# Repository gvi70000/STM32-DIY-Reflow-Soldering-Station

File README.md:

# STM32-DIY-Reflow-Soldering-Station

Warning: Electrical Safety Notice

Before attempting to build or operate the DIY reflow soldering station described in this article, it is imperative to be aware that the hardware operates at 220V AC. Working with high-voltage systems poses inherent risks and demands a thorough understanding of electrical safety precautions.

Introduction:

For electronics enthusiasts seeking a precise and customizable reflow soldering experience, constructing a DIY reflow soldering station is an exciting project. This article provides a detailed overview of the key components and their functionalities, offering a comprehensive guide for building your own soldering station.

Power Supply:

The 220V AC is supplied through the AC Power Entry Module IEC-320 C-14 BVA01/Z0000/02. A Transformer Myrra 47152 steps down the voltage to a crucial 5V, supplying power to essential components such as the BluePill with STM32F302 microcontroller board, fan, and the G3MB-202P 5V DC 1 Channel Solid-State Relay.

User Interface:

The station features a user-friendly interface displayed on a 1.8" ST7735 LCD. User inputs are facilitated through an encoder PEC11R-4220F-S0024 and an RS PRO 17mm Black Potentiometer Knob for 6mm Shaft with a D-shaped grip, ensuring precise control over the soldering process.
Temperature Control and Cooling:

Maintaining optimal temperature is achieved through two strategically positioned 100K ohm 3950 NTC's, calibrated with meticulous accuracy using an FLUKE 51 II Thermometer as a reference. The reflow soldering station incorporates a CFM-6020S-040-320 fan, intelligently activated to cool down the hot plate when needed, ensuring temperature stability.

Operational Modes:

The DIY reflow soldering station offers two distinct modes: rework and reflow. In rework mode, the temperature is kept at a preset value, allowing for precise touch-up soldering. In reflow mode, the temperature follows a preset profile, ideal for soldering components with specific temperature requirements. Both modes utilize a PID controller, ensuring consistent and accurate temperature control throughout the soldering process.

Connections:

The intricate network of connections ensures seamless communication and control within the system. Notable connections include those for SD Card, Encoder, ADC for NTCs, Fan control, Hot plate power control, Buzzer, Encoder button, LCD command, and SPI interface.
Conclusion:

Building your own DIY reflow soldering station offers the satisfaction of creating a precise and reliable tool tailored to your needs. With a robust power supply, intuitive user interface, accurate temperature control, and intelligent cooling, this reflow soldering station provides the necessary features for successful soldering projects. As you embark on this DIY journey, ensure meticulous attention to detail in the assembly and follow safety guidelines to enjoy a versatile and efficient soldering tool for your electronics projects.

The enclosure outline for LASER cutting from 4mm thick acrylic sheet can be downloaded here.

KiCAD Schematic and PCB for controller are available here.

The software for STM32F302 can be downloaded here.

Please note that the PID parameters are generic and you need to change them according to your system, the values are found in Reflow.h file

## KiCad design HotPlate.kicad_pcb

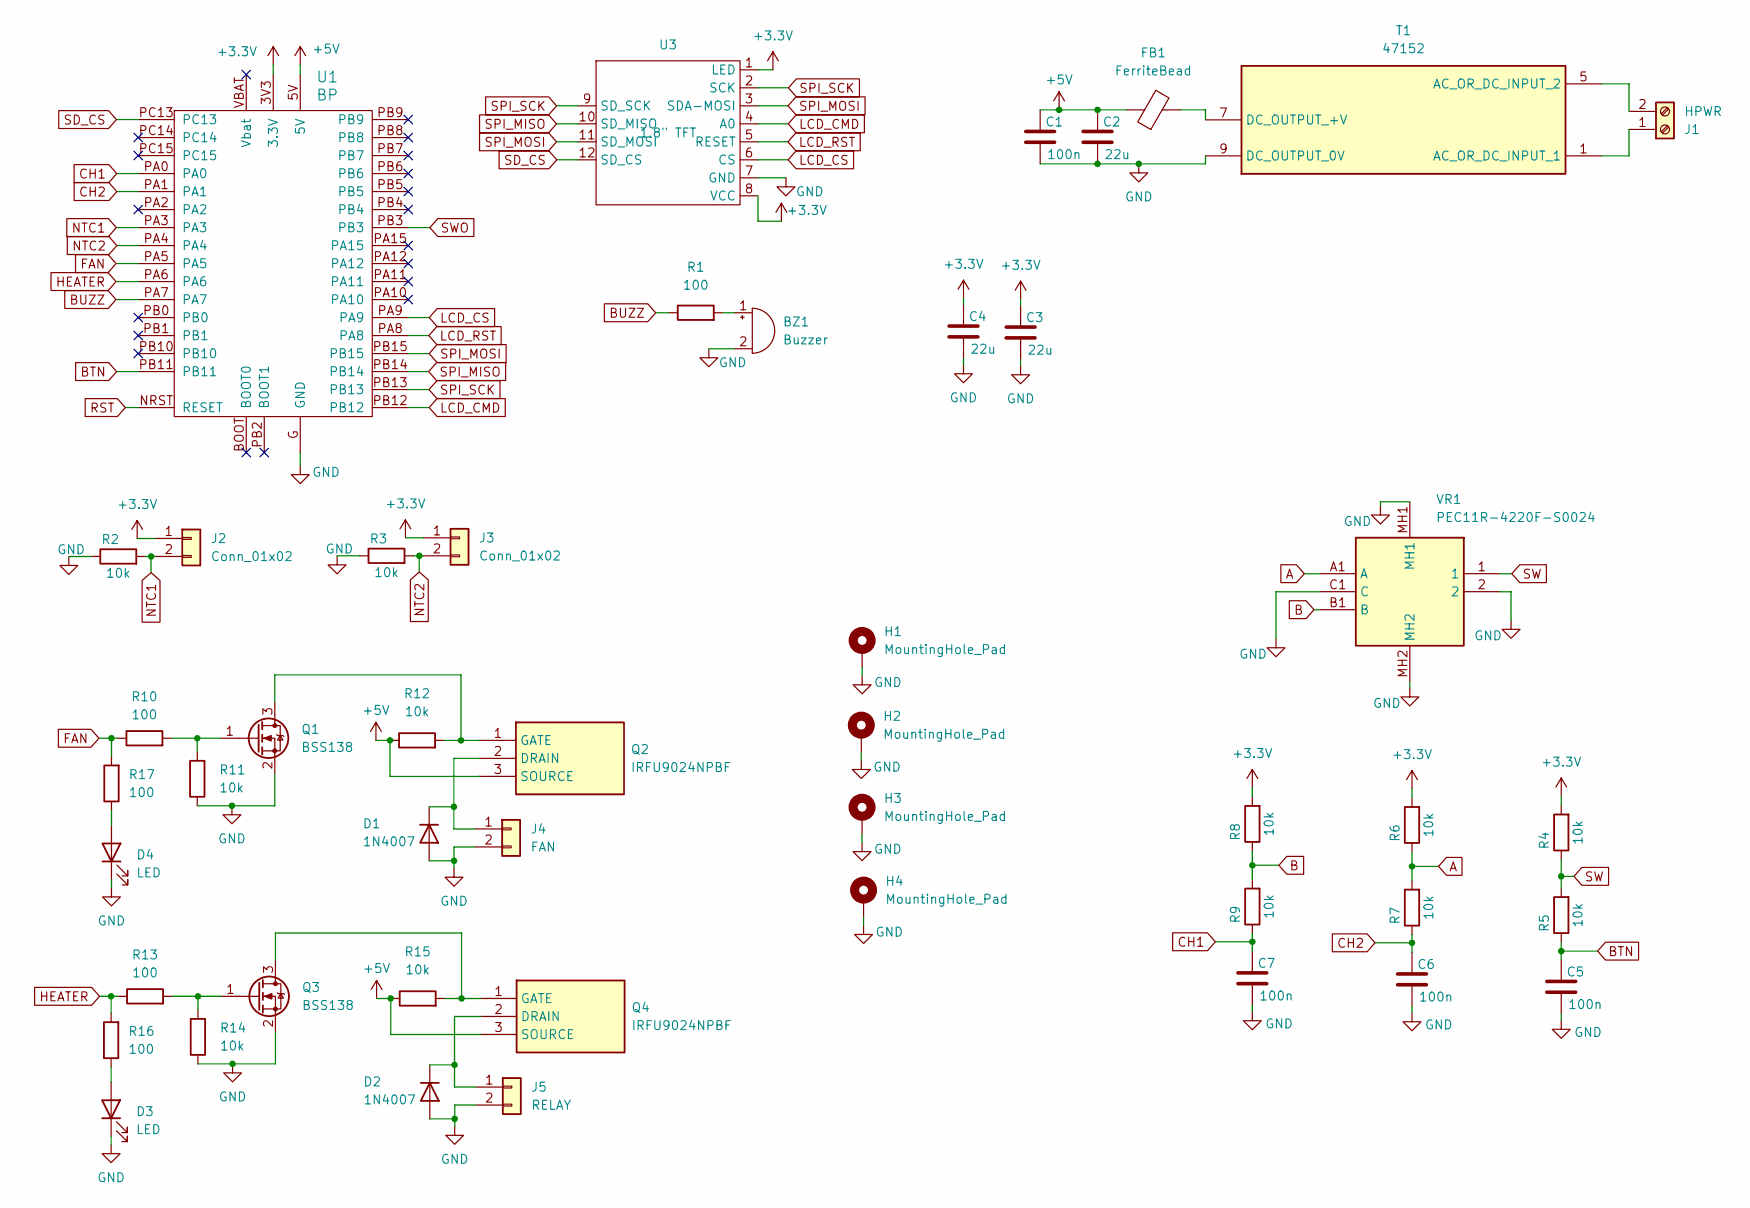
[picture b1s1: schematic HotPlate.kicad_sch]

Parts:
BZ1: Buzzer; Buzzer_TDK_PS1240P02BT_D12.2mm_H6.5mm
C1, C5, C6, C7: 100n; C_0805_2012Metric
C2, C3, C4: 22u; CP_EIA-7343-43_Kemet-X_Pad2.25x2.55mm_HandSolder
D1, D2: 1N4007; D_DO-41_SOD81_P10.16mm_Horizontal
D3, D4: LED; LED_D3.0mm
FB1: FerriteBead; R_0805_2012Metric
H1, H2, H3, H4: MountingHole_Pad; MountingHole_3.2mm_M3_Pad_Via
J1: HPWR; TerminalBlock_Phoenix_PT-1,5-2-5.0-H_1x02_P5.00mm_Horizontal
J2, J3: Conn_01x02; PinHeader_1x02_P2.54mm_Vertical
J4: FAN; PinHeader_1x02_P2.54mm_Vertical
J5: RELAY; PinHeader_1x02_P2.54mm_Vertical
Q1, Q3: BSS138; SOT-23
Q2, Q4: IRFU9024NPBF; TO-251-3_Vertical; Mouser Part Number 942-IRFU9024NPBF
R1: 100; R_0805_2012Metric_Pad1.20x1.40mm_HandSolder
R2, R3, R4, R5, R6, R7, R8, R9: 10k; R_0805_2012Metric_Pad1.20x1.40mm_HandSolder
R10, R13, R16, R17: 100; R_0805_2012Metric
R11, R12, R14, R15: 10k; R_0805_2012Metric
T1: 47152; MYRRA-47121; Manufacturer_Part_Number 47152
U1: BP; blue_pill
U3: 1.8" TFT; 1.8 TFT
VR1: PEC11R-4220F-S0024; PEC11R4220FS0024; Mouser Part Number 652-PEC11R-4220F-S24

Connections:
+3.3V: C3.1, C4.1, J2.1, J3.1, R4.2, R6.2, R8.2, U1.3V3 (3.3V), U3.1 (LED), U3.8 (VCC)
+5V: C1.1, C2.1, FB1.1, Q2.3 (SOURCE), Q4.3 (SOURCE), R12.1, R15.1, U1.5V
A: R6.1, R7.2, VR1.A1 (A)
B: R8.1, R9.2, VR1.B1 (B)
BTN: C5.1, R5.1, U1.PB11
BUZZ: R1.1, U1.PA7
CH1: C7.1, R9.1, U1.PA0
CH2: C6.1, R7.1, U1.PA1
FAN: R10.1, R17.2, U1.PA5
GND: BZ1.2 (+), C1.2, C2.2, C3.2, C4.2, C5.2, C6.2, C7.2, D1.2 (A), D2.2 (A), D3.1 (K), D4.1 (K), H1.1, H2.1, H3.1, H4.1, J4.2, J5.2, Q1.2 (S), Q3.2 (S), R2.1, R3.1, R11.1, R14.1, T1.9 (DC_OUTPUT_0V), U1.G (GND), U3.7 (GND), VR1.2, VR1.C1 (C), VR1.MH1, VR1.MH2
HEATER: R13.1, R16.2, U1.PA6
LCD_CMD: U1.PB12, U3.4 (A0)
LCD_CS: U1.PA9, U3.6 (CS)
LCD_RST: U1.PA8, U3.5 (RESET)
NTC1: J2.2, R2.2, U1.PA3
NTC2: J3.2, R3.2, U1.PA4
unnamed: BZ1.1 (-), R1.2
unnamed: D1.1 (K), J4.1, Q2.2 (DRAIN)
unnamed: D2.1 (K), J5.1, Q4.2 (DRAIN)
unnamed: D3.2 (A), R16.1
unnamed: D4.2 (A), R17.1
unnamed: J1.1, T1.1 (AC_OR_DC_INPUT_1)
unnamed: J1.2, T1.5 (AC_OR_DC_INPUT_2)
unnamed: Q1.3 (D), Q2.1 (GATE), R12.2
unnamed: Q1.1 (G), R10.2, R11.2
unnamed: Q3.3 (D), Q4.1 (GATE), R15.2
unnamed: Q3.1 (G), R13.2, R14.2
unnamed: FB1.2, T1.7 (DC_OUTPUT_+V)
RST: U1.NRST (RESET)
SD_CS: U1.PC13, U3.12 (SD_CS)
SPI_MISO: U1.PB14, U3.10 (SD_MISO)
SPI_MOSI: U1.PB15, U3.3 (SDA-MOSI), U3.11 (SD_MOSI)
SPI_SCK: U1.PB13, U3.2 (SCK), U3.9 (SD_SCK)
SW: R4.1, R5.2, VR1.1
SWO: U1.PB3

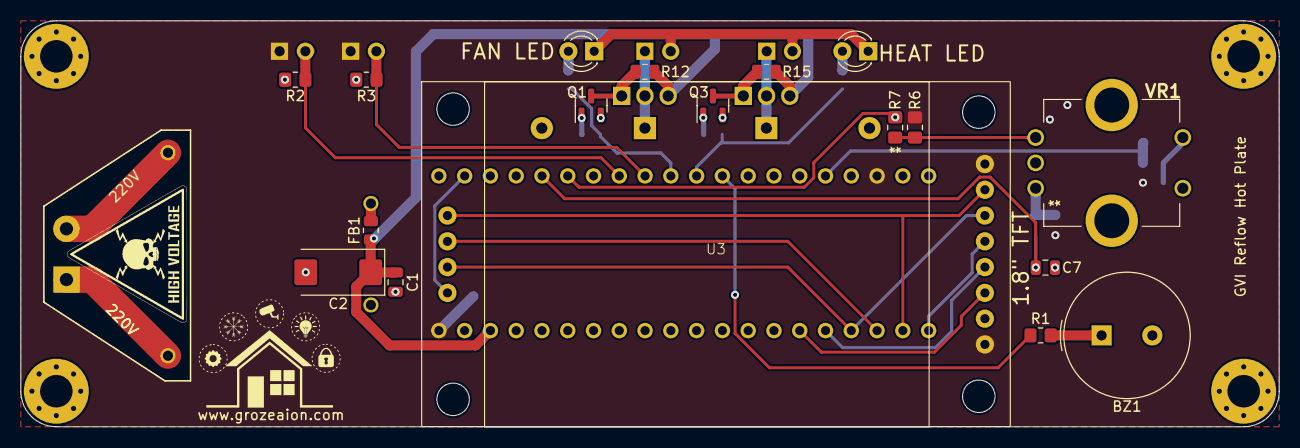
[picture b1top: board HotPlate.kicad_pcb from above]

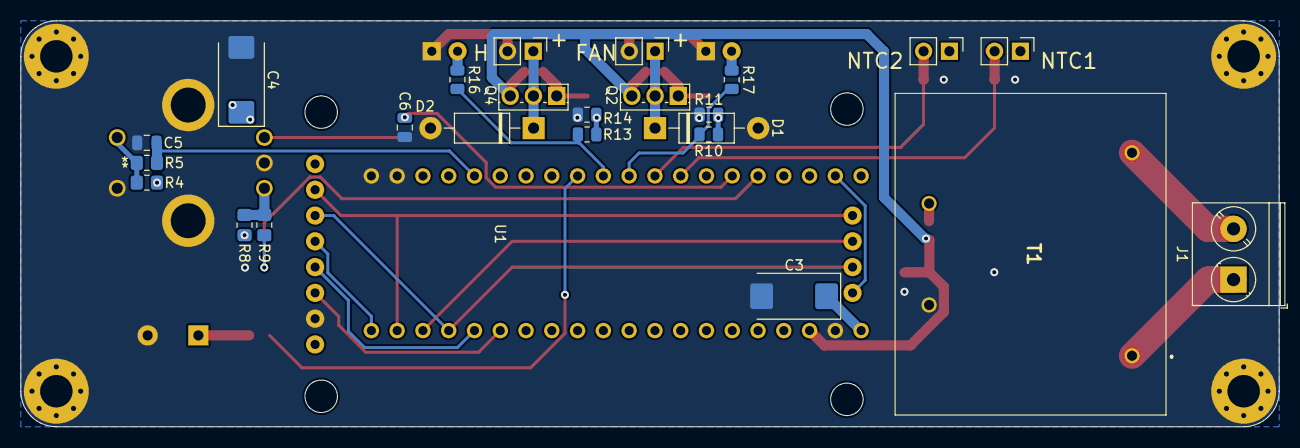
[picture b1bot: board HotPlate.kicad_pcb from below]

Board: 2 copper layers, 124.0 x 40.0 mm, 47 parts (25 on the bottom side), 33 nets.

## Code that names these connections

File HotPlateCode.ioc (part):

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Mcu.Name=STM32F302C(B-C)Tx
Mcu.Package=LQFP48
Mcu.UserName=STM32F302CCTx
PA0.Signal=S_TIM2_CH1_ETR
PA1.Signal=S_TIM2_CH2
PA13.Mode=Trace_Asynchronous_SW
PA13.Signal=SYS_JTMS-SWDIO
PA14.Mode=Trace_Asynchronous_SW
PA14.Signal=SYS_JTCK-SWCLK
PA3.GPIOParameters=GPIO_Label
PA3.GPIO_Label=NTC1
PA3.Mode=IN4-Single-Ended
PA3.Signal=ADC1_IN4
PA4.GPIOParameters=GPIO_Label
PA4.GPIO_Label=NTC2
PA4.Mode=IN1-Single-Ended
PA4.Signal=ADC2_IN1
PA5.GPIOParameters=GPIO_Label
PA5.GPIO_Label=FAN
PA5.Signal=GPIO_Output
PA6.GPIOParameters=GPIO_Label
PA6.GPIO_Label=HEATER
PA6.Signal=GPIO_Output
PA7.Mode=PWM Generation1 CH1N
PA7.Signal=TIM1_CH1N
PA8.GPIOParameters=GPIO_Label
PA8.GPIO_Label=LCD_RST
PA8.Signal=GPIO_Output
PA9.GPIOParameters=GPIO_Label
PA9.GPIO_Label=LCD_CS
PA9.Signal=GPIO_Output
PB11.GPIOParameters=GPIO_Label
PB11.GPIO_Label=BTN
PB11.Signal=GPXTI11
PB12.GPIOParameters=GPIO_Label
PB12.GPIO_Label=LCD_CMD
PB12.Signal=GPIO_Output
PB13.Mode=Full_Duplex_Master
PB13.Signal=SPI2_SCK
PB14.Mode=Full_Duplex_Master
PB14.Signal=SPI2_MISO
PB15.Mode=Full_Duplex_Master
PB15.Signal=SPI2_MOSI
PB3.Mode=Trace_Asynchronous_SW
PB3.Signal=SYS_JTDO-TRACESWO
PC13.Signal=GPIO_Output
PF0-OSC_IN.Mode=HSE-External-Oscillator
PF0-OSC_IN.Signal=RCC_OSC_IN
PF1-OSC_OUT.Mode=HSE-External-Oscillator
PF1-OSC_OUT.Signal=RCC_OSC_OUT
RCC.HSEPLLFreq_Value=8000000
RCC.HSE_VALUE=8000000
RCC.SYSCLKFreq_VALUE=72000000
RCC.SYSCLKSourceVirtual=RCC_SYSCLKSOURCE_PLLCLK
board=custom
